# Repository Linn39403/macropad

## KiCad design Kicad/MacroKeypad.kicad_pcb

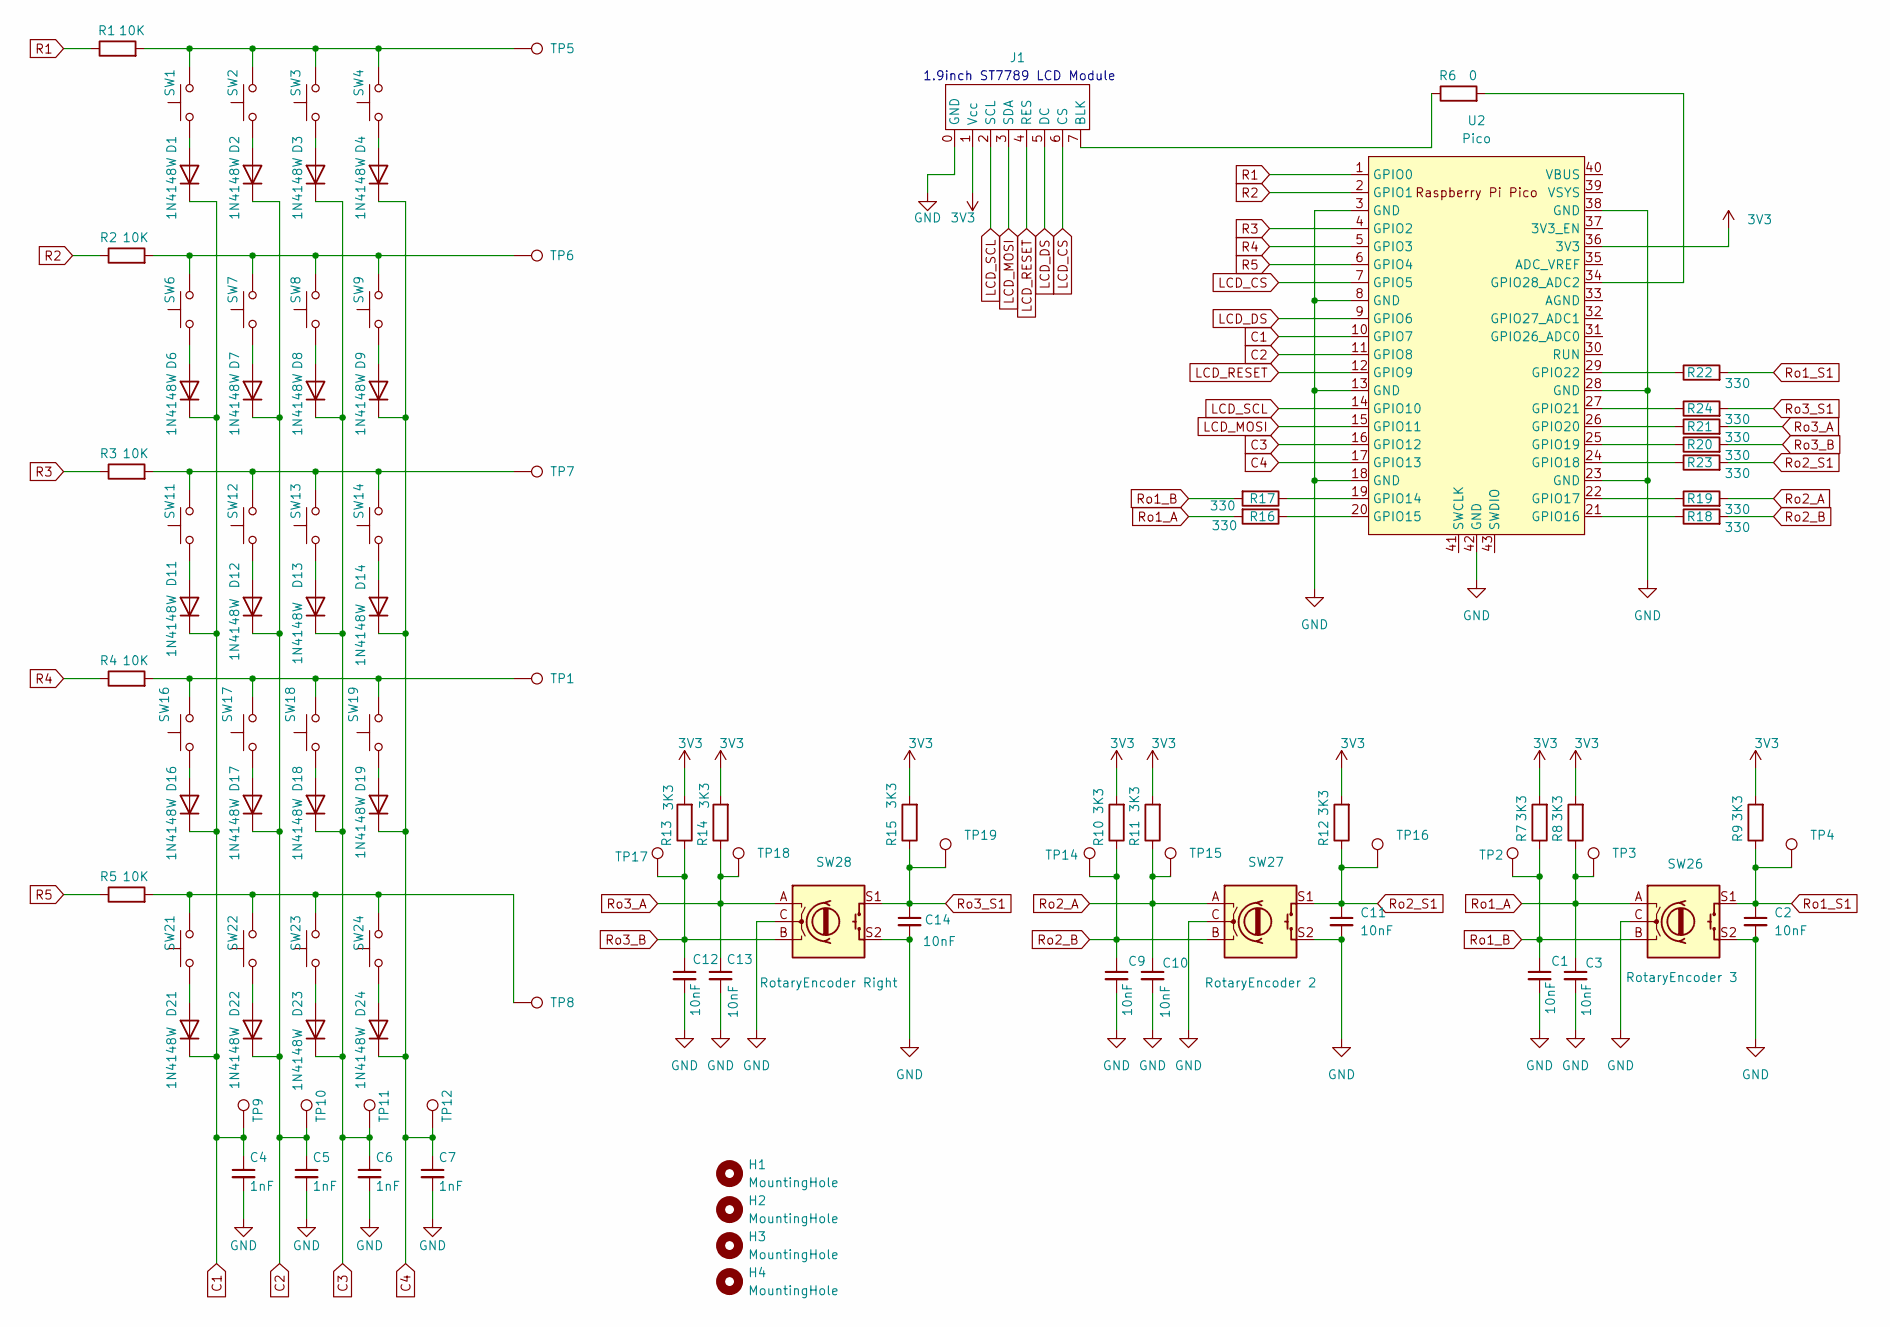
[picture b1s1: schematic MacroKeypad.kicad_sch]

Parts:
C1, C2, C3, C9, C10, C11, C12, C13, C14: 10nF; C_0603_1608Metric_Pad1.08x0.95mm_HandSolder
C4, C5, C6, C7: 1nF; C_0603_1608Metric_Pad1.08x0.95mm_HandSolder
D1, D2, D3, D4, D6, D7, D8, D9, D11, D12, D13, D14, D16, D17, D18, D19, D21, D22, D23, D24: 1N4148W; D_SOD-123
H1, H2, H3, H4: MountingHole; MountingHole_3.2mm_M3_ISO7380_Pad
J1: st7789_1.9inch
R1, R2, R3, R4, R5: 10K; R_0603_1608Metric_Pad0.98x0.95mm_HandSolder
R6: 0; R_0603_1608Metric_Pad0.98x0.95mm_HandSolder
R7, R8, R9, R10, R11, R12, R13, R14, R15: 3K3; R_0603_1608Metric_Pad0.98x0.95mm_HandSolder
R16, R17, R18, R19, R20, R21, R22, R23, R24: 330; R_0603_1608Metric_Pad0.98x0.95mm_HandSolder
SW1: SW_Push; SW_Cherry_MX_1.00u_PCB
SW2, SW3, SW4, SW6, SW7, SW8, SW9, SW11, SW12, SW13, SW14, SW16, SW17, SW18, SW19, SW21, SW22, SW23, SW24: SW_Push; SW_Cherry_MX_1.00u_PCB_3D
SW26: RotaryEncoder 3; RotaryEncoder_Alps_EC11E-Switch_Vertical_H20mm_3D
SW27: RotaryEncoder 2; RotaryEncoder_Alps_EC11E-Switch_Vertical_H20mm_3D
SW28: RotaryEncoder Right; RotaryEncoder_Alps_EC11E-Switch_Vertical_H20mm_3D
TP1, TP2, TP3, TP4, TP5, TP6, TP7, TP8, TP9, TP10, TP11, TP12, TP14, TP15, TP16, TP17, TP18, TP19: TestPoint; TestPoint_Pad_D1.0mm
U2: Pico; RPi_Pico_SMD_TH

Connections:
3V3: J1.1 (Vcc), R7.2, R8.2, R9.2, R10.2, R11.2, R12.2, R13.2, R14.2, R15.2, U2.36 (3V3)
C1: C4.1, D1.1 (K), D6.1 (K), D11.1 (K), D16.1 (K), D21.1 (K), TP9.1, U2.10 (GPIO7)
C2: C5.1, D2.1 (K), D7.1 (K), D12.1 (K), D17.1 (K), D22.1 (K), TP10.1, U2.11 (GPIO8)
C3: C6.1, D3.1 (K), D8.1 (K), D13.1 (K), D18.1 (K), D23.1 (K), TP11.1, U2.16 (GPIO12)
C4: C7.1, D4.1 (K), D9.1 (K), D14.1 (K), D19.1 (K), D24.1 (K), TP12.1, U2.17 (GPIO13)
GND: C1.2, C2.2, C3.2, C4.2, C5.2, C6.2, C7.2, C9.2, C10.2, C11.2, C12.2, C13.2, C14.2, J1.0 (GND), SW26.C, SW26.S2, SW27.C, SW27.S2, SW28.C, SW28.S2, U2.3 (GND), U2.8 (GND), U2.13 (GND), U2.18 (GND), U2.23 (GND), U2.28 (GND), U2.38 (GND), U2.42 (GND)
LCD_CS: J1.6 (CS), U2.7 (GPIO5)
LCD_DS: J1.5 (DC), U2.9 (GPIO6)
LCD_MOSI: J1.3 (SDA), U2.15 (GPIO11)
LCD_RESET: J1.4 (RES), U2.12 (GPIO9)
LCD_SCL: J1.2 (SCL), U2.14 (GPIO10)
unnamed: D1.2 (A), SW1.1
unnamed: D2.2 (A), SW2.1
unnamed: D3.2 (A), SW3.1
unnamed: D4.2 (A), SW4.1
unnamed: D6.2 (A), SW6.1
unnamed: D7.2 (A), SW7.1
unnamed: D8.2 (A), SW8.1
unnamed: D9.2 (A), SW9.1
unnamed: D11.2 (A), SW11.1
unnamed: D12.2 (A), SW12.1
unnamed: D13.2 (A), SW13.1
unnamed: D14.2 (A), SW14.1
unnamed: D16.2 (A), SW16.1
unnamed: D17.2 (A), SW17.1
unnamed: D18.2 (A), SW18.1
unnamed: D19.2 (A), SW19.1
unnamed: D21.2 (A), SW21.1
unnamed: D22.2 (A), SW22.1
unnamed: D23.2 (A), SW23.1
unnamed: D24.2 (A), SW24.1
unnamed: J1.7 (BLK), R6.1
unnamed: R1.2, SW1.2, SW2.2, SW3.2, SW4.2, TP5.1
unnamed: R2.2, SW6.2, SW7.2, SW8.2, SW9.2, TP6.1
unnamed: R3.2, SW11.2, SW12.2, SW13.2, SW14.2, TP7.1
unnamed: R4.2, SW16.2, SW17.2, SW18.2, SW19.2, TP1.1
unnamed: R5.2, SW21.2, SW22.2, SW23.2, SW24.2, TP8.1
unnamed: R17.1, U2.19 (GPIO14)
unnamed: R16.1, U2.20 (GPIO15)
unnamed: R18.1, U2.21 (GPIO16)
unnamed: R19.1, U2.22 (GPIO17)
unnamed: R23.1, U2.24 (GPIO18)
unnamed: R20.1, U2.25 (GPIO19)
unnamed: R21.1, U2.26 (GPIO20)
unnamed: R24.1, U2.27 (GPIO21)
unnamed: R22.1, U2.29 (GPIO22)
unnamed: R6.2, U2.34 (GPIO28_ADC2)
R1: R1.1, U2.1 (GPIO0)
R2: R2.1, U2.2 (GPIO1)
R3: R3.1, U2.4 (GPIO2)
R4: R4.1, U2.5 (GPIO3)
R5: R5.1, U2.6 (GPIO4)
Ro1_A: C3.1, R8.1, R16.2, SW26.A, TP3.1
Ro1_B: C1.1, R7.1, R17.2, SW26.B, TP2.1
Ro1_S1: C2.1, R9.1, R22.2, SW26.S1, TP4.1
Ro2_A: C10.1, R11.1, R19.2, SW27.A, TP15.1
Ro2_B: C9.1, R10.1, R18.2, SW27.B, TP14.1
Ro2_S1: C11.1, R12.1, R23.2, SW27.S1, TP16.1
Ro3_A: C13.1, R14.1, R21.2, SW28.A, TP18.1
Ro3_B: C12.1, R13.1, R20.2, SW28.B, TP17.1
Ro3_S1: C14.1, R15.1, R24.2, SW28.S1, TP19.1

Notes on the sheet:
1.9inch ST7789 LCD Module

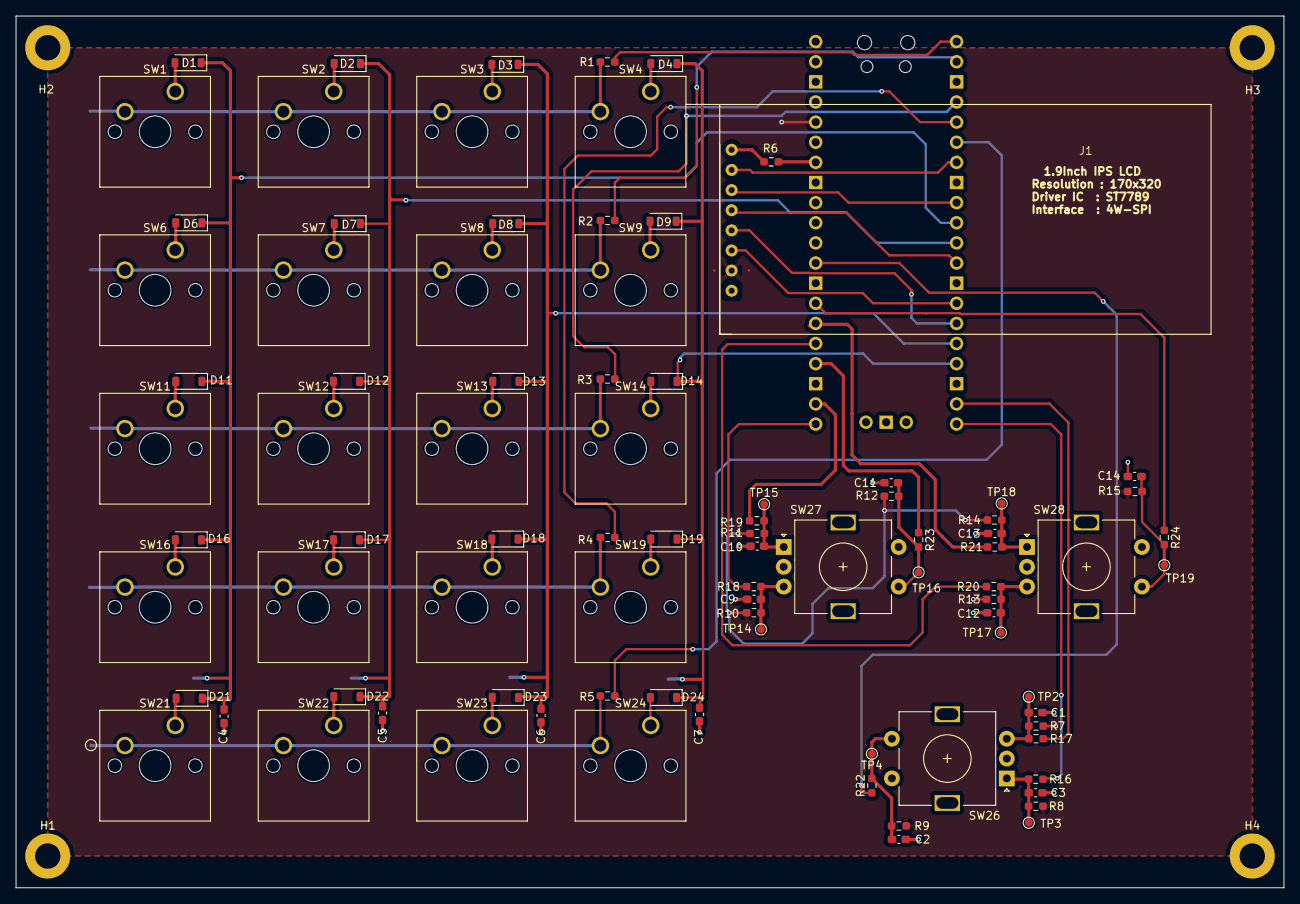
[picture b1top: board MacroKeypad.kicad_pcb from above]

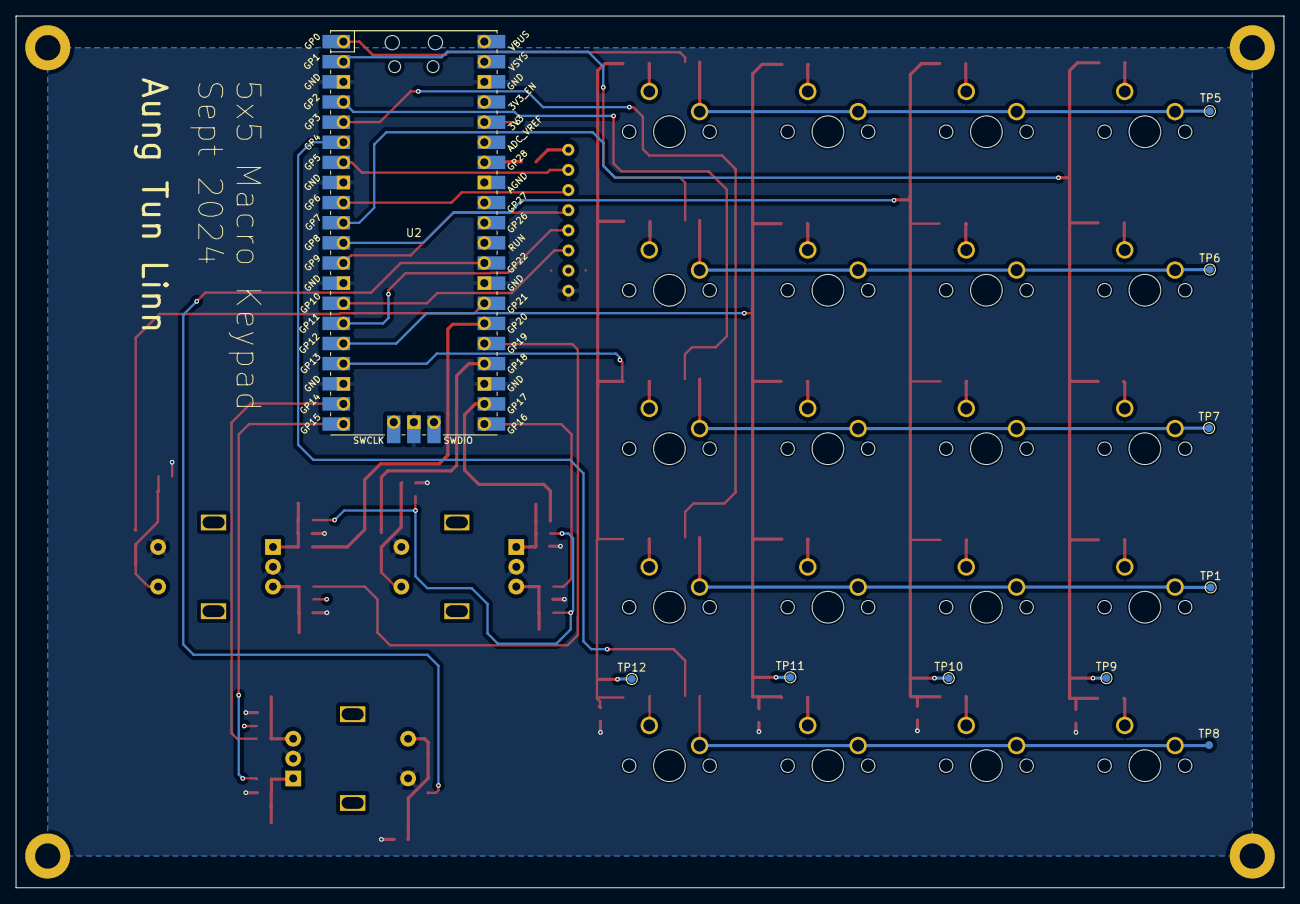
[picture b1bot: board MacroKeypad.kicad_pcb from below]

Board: 2 copper layers, 160.0 x 110.0 mm, 104 parts (9 on the bottom side), 61 nets.

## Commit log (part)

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2024-11-02 commit the Kicad design files
2024-11-03 commit developing qmk firmware
2025-05-01 lcd is working with 4 keypad layers, and two buttons on left and right rotary encoder buttons to move the layers
2025-05-05 update the host script and clienet side to detect the two running applicaions, total commander and calculator
2025-05-05 rename the firmware folder name
2025-05-10 clean up and change the screen from tabl view to mutli screens currently only num pad and total commander screens are created.
2025-05-11 refactor the code
2025-05-12 add window volume control arc
2025-05-12 add ring buffer to tranfer volume control value from HID to house keeping task update the LVGL arc animation based on the update freq value ( smoother )
2025-05-17 refactor code for the button create fun
2025-05-19 refactor key press handle code for layers
2025-05-24 refactor keypad_screen
2025-05-25 add range limit for sound volume arc
2025-05-27 update host script for robutness
2025-05-29 change 1.9inch lcd to 2inch and add label in each layers
2025-05-29 clone browser layer from total commander layer
2025-05-30 refactor the code using X macro in keymap .c & .h
2025-05-30 refactor the code using X macro in screens.c & keymap.h
2025-05-31 refactor keymaps array using X macro
2025-06-08 add more browser shortcuts and relocate the keymaps files
2025-06-09 add fun keys layer
2025-06-09 update fun keys
2025-06-10 alight the text to the center of the screen
2025-06-14 modify rotary encoder callback funtion to accept the button press state
2025-06-15 add house keeping fun call
2025-06-16 develop in progress : only 2 layers are enabled
2025-06-18 develop in progress : add browser layer
2025-06-18 develop in progress : add funkeys layer
2025-06-19 develop in progress : add win explorer layer
2025-06-22 develop in progress :add lock screen layer
2025-07-19 develop in progress : fix the host side still can send command during macropad is locked
2025-08-24 set all the same color format
2025-08-24 add special layer ( but it's not pushed to github )
